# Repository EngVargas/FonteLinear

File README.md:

# Fonte Linear
Projeto de uma fonte linear, com transformador, baseada em reguladores 78xx, 79xx e LM317.
<br><br><br>

Vídeos explicando o projeto (youtube) disponíveis em:

*Parte 1:* Introdução realizado no SMath (4:10): https://youtu.be/99YkMpbQ9RE

*Parte 2:* Topologia (circuito) da fonte em questão (13:12): https://youtu.be/afl0XzgpsDg

*Parte 3:* Projeto realizado no SMath (16:18): https://youtu.be/Y6MiDEMt3rU

*Parte 4:* Simulações realizadas no LTspice (9:07): https://youtu.be/Sk8upL2aWj8

*Parte 5:* Placa (*board*) realizada no KiCad (3:58): https://youtu.be/-oL63cRfRww

*Parte 6:* Corroendo a placa de fenolite (x:xx): Falta gravar.

*Parte 7:* Solda dos componentes PTH (*through-hole*) (x:xx): Falta gravar.

<br><br><br>

Playlist completa: https://www.youtube.com/playlist?list=PLbFFLnJpBtKtD-fQlKbGmZ5WMdUnZlrNB

Canal do Youtube:  https://www.youtube.com/channel/UCZTJobFHQ0Zxr3MwumCp64A

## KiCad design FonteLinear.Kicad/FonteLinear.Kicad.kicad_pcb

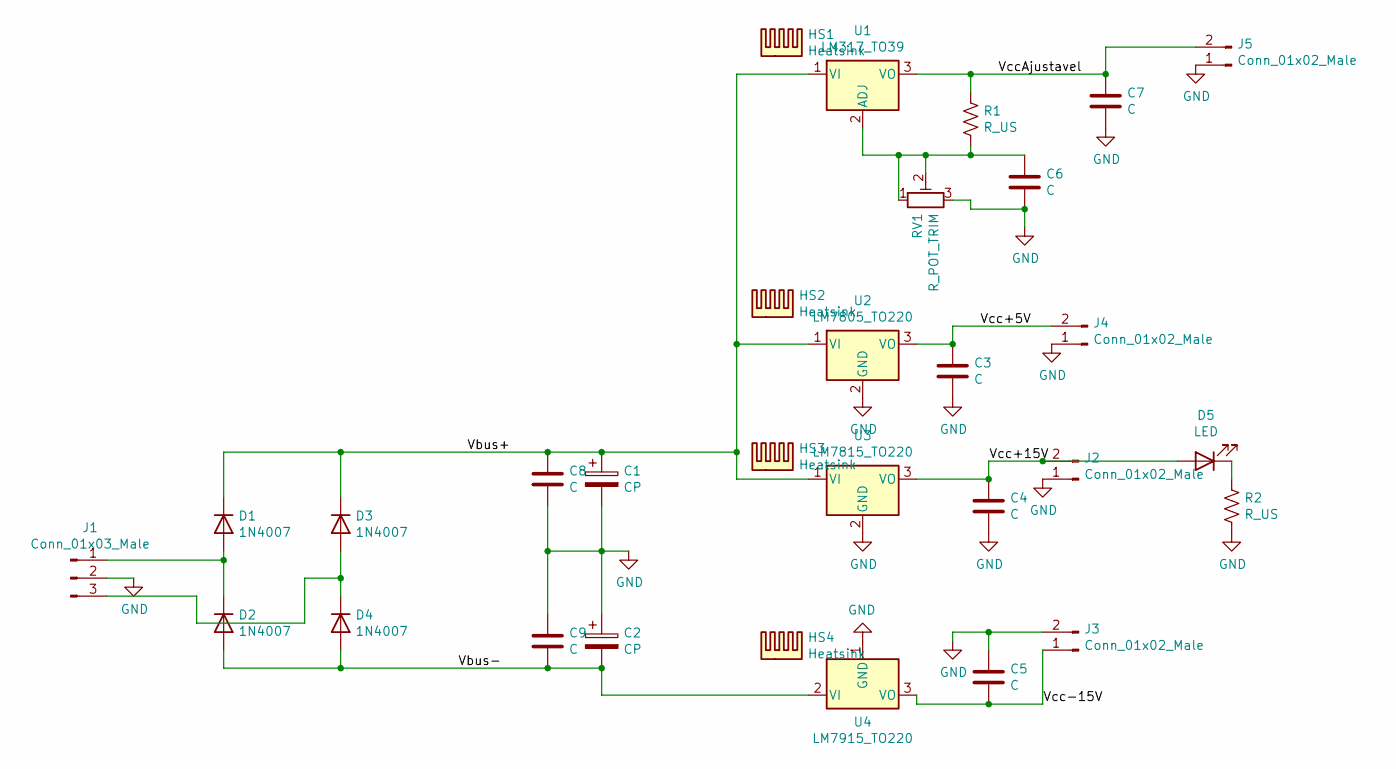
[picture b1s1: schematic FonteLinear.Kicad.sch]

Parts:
C1, C2: CP; CP_Radial_D16.0mm_P7.50mm
C3, C4, C5, C6, C7, C8, C9: C; C_Disc_D5.0mm_W2.5mm_P2.50mm
D1, D2, D3, D4: 1N4007; D_DO-41_SOD81_P10.16mm_Horizontal
D5: LED; LED_D5.0mm
HS1, HS2, HS3, HS4: Heatsink; Heatsink_Stonecold_HS-132_32x14mm_2xFixation1.5mm
J1: Conn_01x03_Male; PinHeader_1x03_P2.54mm_Vertical
J2, J3, J4, J5: Conn_01x02_Male; PinHeader_1x02_P2.54mm_Vertical
R1, R2: R_US; R_Axial_DIN0207_L6.3mm_D2.5mm_P7.62mm_Horizontal
RV1: R_POT_TRIM; Potentiometer_Bourns_3005_Horizontal
U1: LM317_TO39; TO-220-3_Vertical
U2: LM7805_TO220; TO-220-3_Vertical
U3: LM7815_TO220; TO-220-3_Vertical
U4: LM7915_TO220; TO-220-3_Vertical

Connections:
/Vbus+: C1.1, C8.1, D1.1 (K), D3.1 (K), U1.1 (VI), U2.1 (VI), U3.1 (VI)
/Vbus-: C2.2, C9.2, D2.2 (A), D4.2 (A), U4.2 (VI)
/Vcc+5V: C3.1, J4.2, U2.3 (VO)
/Vcc+15V: C4.1, D5.2 (A), J2.2, U3.3 (VO)
/Vcc-15V: C5.2, J3.1, U4.3 (VO)
/VccAjustavel: C7.1, J5.2, R1.1, U1.3 (VO)
GND: C1.2, C2.1, C3.2, C4.2, C5.1, C6.2, C7.2, C8.2, C9.1, J1.2, J2.1, J3.2, J4.1, J5.1, R2.2, RV1.3, U2.2 (GND), U3.2 (GND), U4.1 (GND)
unnamed: C6.1, R1.2, RV1.1, RV1.2, U1.2 (ADJ)
unnamed: D1.2 (A), D2.1 (K), J1.1
unnamed: D3.2 (A), D4.1 (K), J1.3
unnamed: D5.1 (K), R2.1

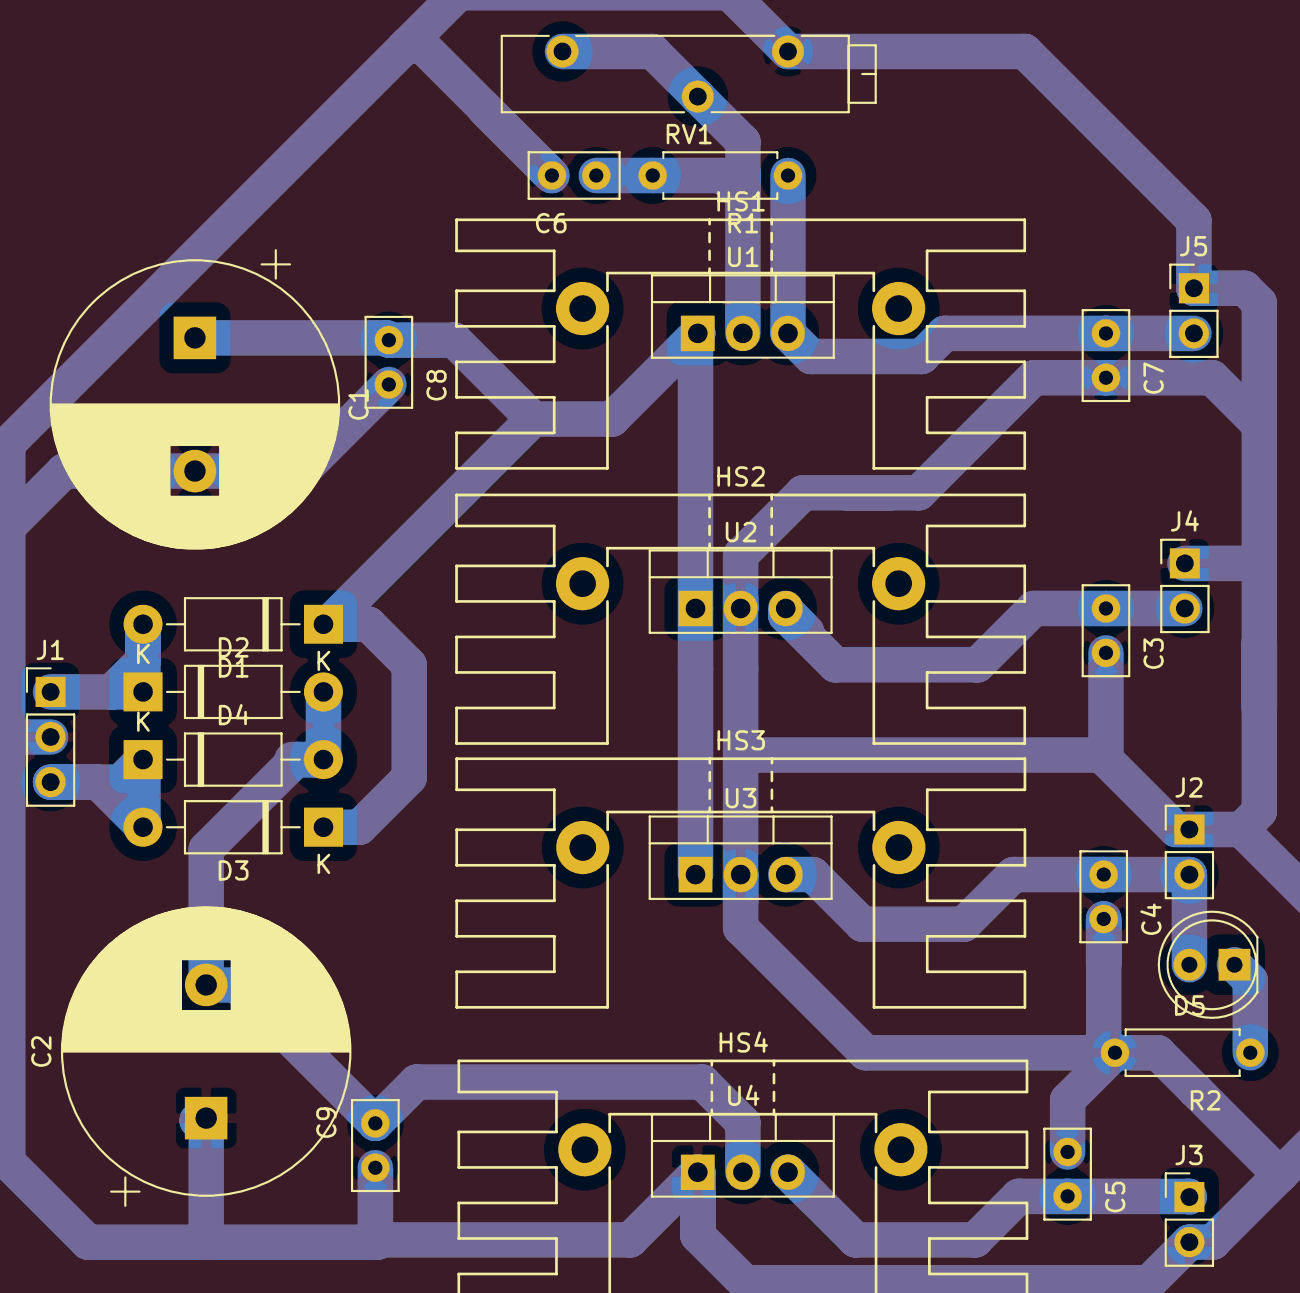
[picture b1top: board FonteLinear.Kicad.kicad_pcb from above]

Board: 2 copper layers, 30 parts (0 on the bottom side), 11 nets.
